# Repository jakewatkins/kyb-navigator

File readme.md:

# Navigator keypad
This is my attempt at creating a wireless macro keypad to augment my wireless Corne keyboards.  The goal is to create a macro keypad with a dislay, led back lighting and led per key lighting on MX switches.  To make things simple (I think) I want to use the same Nice!Nano controller the Corne uses so I get bluetooth and usb-c out of the box.  Further I should be able to use ZMK to setup the firmware and perform the keyboard mappping sense this will basically be a Corne with fewer keys.

Total overkill for a macro keypad. 
The plan is to use ErgoGen to create the layout and produce the files KiCAD needs to create the PCB.

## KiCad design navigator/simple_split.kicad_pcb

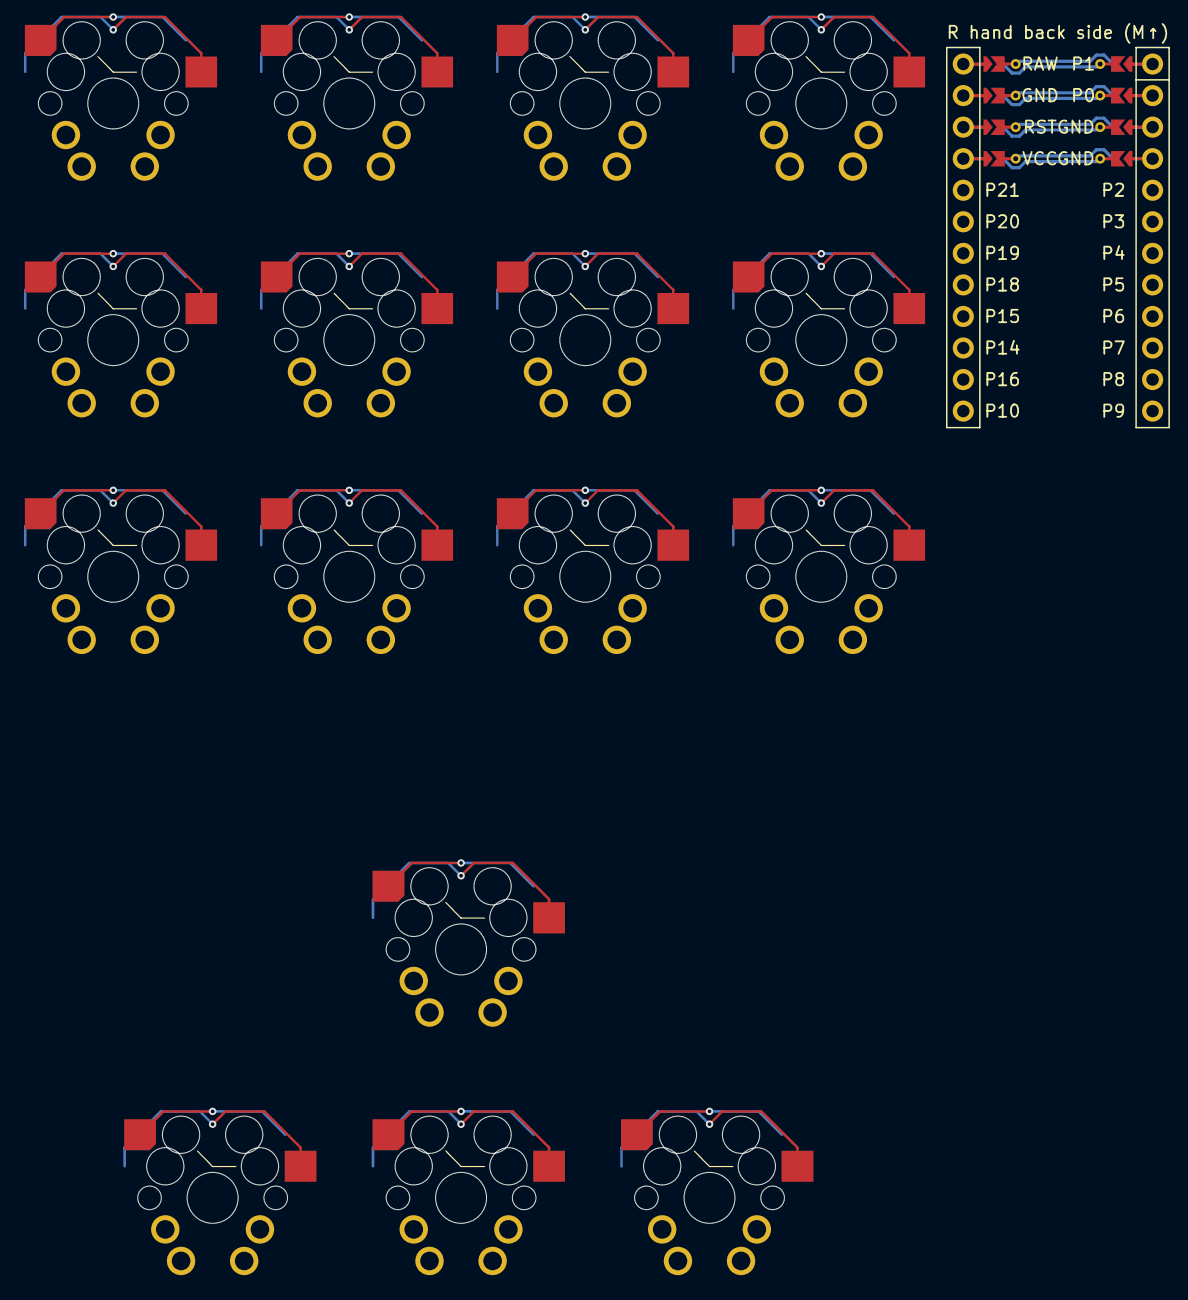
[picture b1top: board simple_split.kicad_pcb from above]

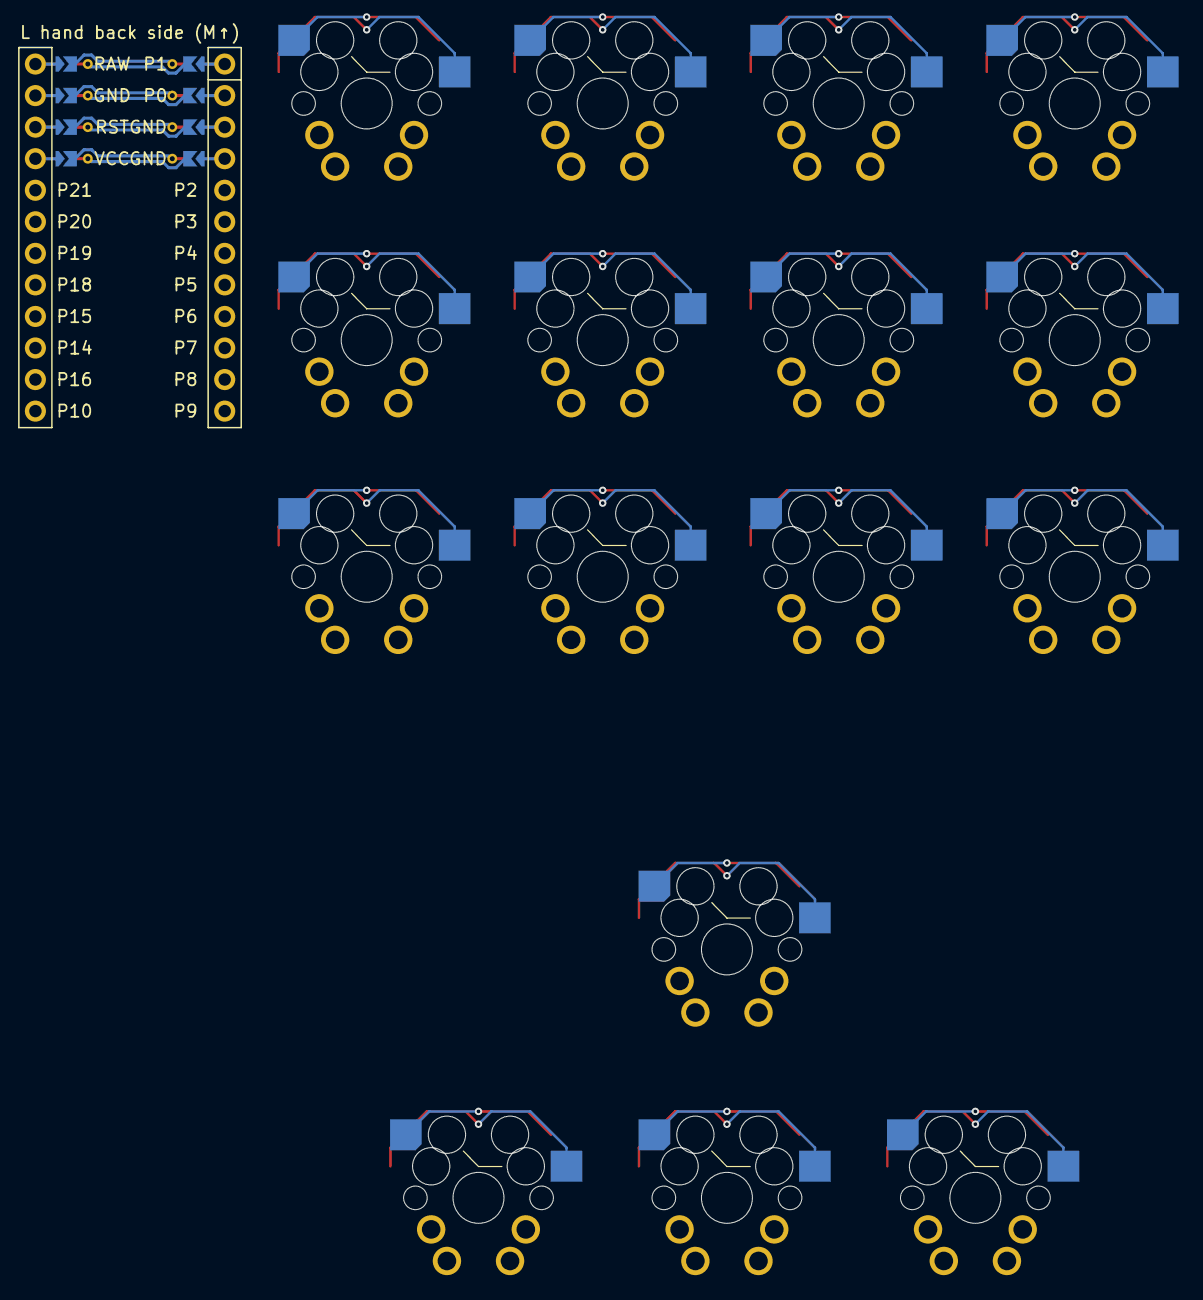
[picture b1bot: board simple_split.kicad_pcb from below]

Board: 2 copper layers, 17 parts (16 on the bottom side), 13 nets.

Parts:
MCU1: mcu_nice_nano
S1, S2, S3, S4, S5, S6, S7, S8, S9, S10, S11, S12, S13, S14, S15, S16: switch_mx

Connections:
GND: MCU1.103, MCU1.104, MCU1.123, S1.1, S2.1, S3.1, S4.1, S5.1, S6.1, S7.1, S8.1, S9.1, S10.1, S11.1, S12.1, S13.1, S14.1, S15.1, S16.1
matrix_inner_bottom: MCU1.9, S10.2
matrix_inner_home: MCU1.101, S11.2
matrix_inner_top: MCU1.20, S12.2
matrix_middle_bottom: MCU1.7, S7.2
matrix_middle_home: MCU1.14, S8.2
matrix_middle_top: MCU1.18, S9.2
matrix_pinky_bottom: MCU1.5, S1.2
matrix_pinky_home: MCU1.16, S2.2
matrix_pinky_top: MCU1.10, S3.2
matrix_ring_bottom: MCU1.6, S4.2
matrix_ring_home: MCU1.15, S5.2
matrix_ring_top: MCU1.17, S6.2

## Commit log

2025-06-08 adding readme
